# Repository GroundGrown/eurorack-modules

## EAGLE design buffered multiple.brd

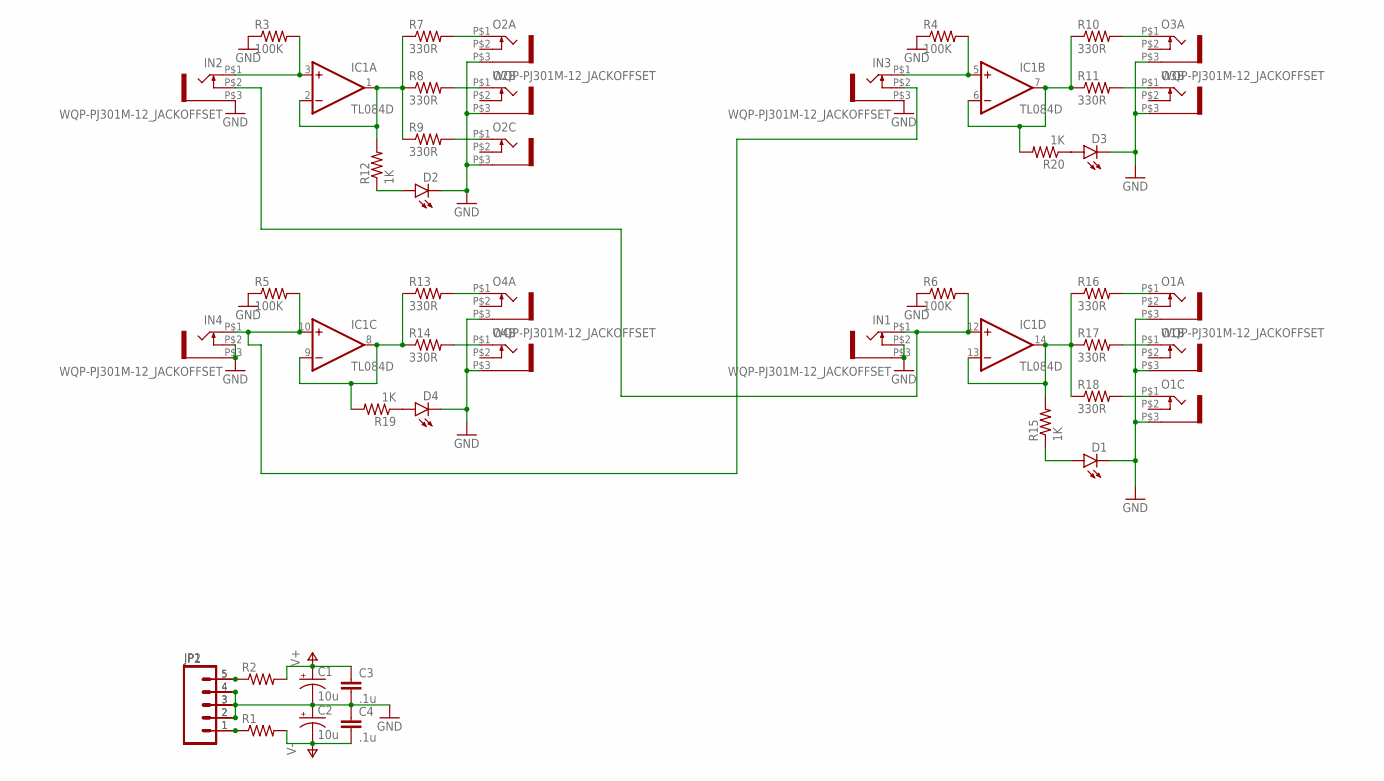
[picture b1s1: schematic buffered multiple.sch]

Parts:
C1, C2: 10u; EIA3216-KIT
C3, C4: .1u; 0805
D1, D2, D3, D4: LED3MM
IC1: TL084D; SO14
IN1, IN2, IN3, IN4: WQP-PJ301M-12_JACKOFFSET
JP1, JP2: M05PTH; 1X05
O1A, O2A, O3A, O4A: WQP-PJ301M-12_JACKOFFSET
O1B, O1C, O2B, O2C, O3B, O4B: WQP-PJ301M-12_JACK
R1, R2: RESISTOR0805-RES; 0805
R3, R4, R5, R6: 100K; 0805
R7, R8, R9, R10, R11, R13, R14, R16, R17, R18: 330R; 0805
R12, R15, R19, R20: 1K; 0805

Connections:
GND: C1.C (-), C2.A (+), C3.2, C4.1, D1.K (C), D2.K (C), D3.K (C), D4.K (C), IN1.P$2 (3), IN1.P$3 (1), IN2.P$3 (1), IN3.P$3 (1), IN4.P$2 (3), IN4.P$3 (1), JP1.2, JP1.3, JP1.4, JP2.2, JP2.3, JP2.4, O1A.P$3 (1), O1B.P$3 (1), O1C.P$3 (1), O2A.P$3 (1), O2B.P$3 (1), O2C.P$3 (1), O3A.P$3 (1), O3B.P$3 (1), O4A.P$3 (1), O4B.P$3 (1), R3.1, R4.1, R5.1, R6.1
unnamed: JP1.1, JP2.1, R1.1
unnamed: JP1.5, JP2.5, R2.1
unnamed: IC1.12 (+IN), IN1.P$1 (2), IN2.P$2 (3), R6.2
unnamed: IC1.10 (+IN), IN3.P$2 (3), IN4.P$1 (2), R5.2
unnamed: IC1.3 (+IN), IN2.P$1 (2), R3.2
unnamed: IC1.5 (+IN), IN3.P$1 (2), R4.2
unnamed: IC1.1 (OUT), IC1.2 (-IN), R7.1, R8.1, R9.1, R12.2
unnamed: O2A.P$1 (2), R7.2
unnamed: O2B.P$1 (2), R8.2
unnamed: O2C.P$1 (2), R9.2
unnamed: IC1.8 (OUT), IC1.9 (-IN), R13.1, R14.1, R19.2
unnamed: O4A.P$1 (2), R13.2
unnamed: O4B.P$1 (2), R14.2
unnamed: IC1.6 (-IN), IC1.7 (OUT), R10.1, R11.1, R20.2
unnamed: O3A.P$1 (2), R10.2
unnamed: O3B.P$1 (2), R11.2
unnamed: D4.A, R19.1
unnamed: IC1.13 (-IN), IC1.14 (OUT), R15.2, R16.1, R17.1, R18.1
unnamed: O1A.P$1 (2), R16.2
unnamed: O1B.P$1 (2), R17.2
unnamed: O1C.P$1 (2), R18.2
unnamed: D3.A, R20.1
unnamed: D1.A, R15.1
unnamed: D2.A, R12.1
V+: C1.A (+), C3.1, IC1.4 (V+), R2.2
V-: C2.C (-), C4.2, IC1.11 (V-), R1.2

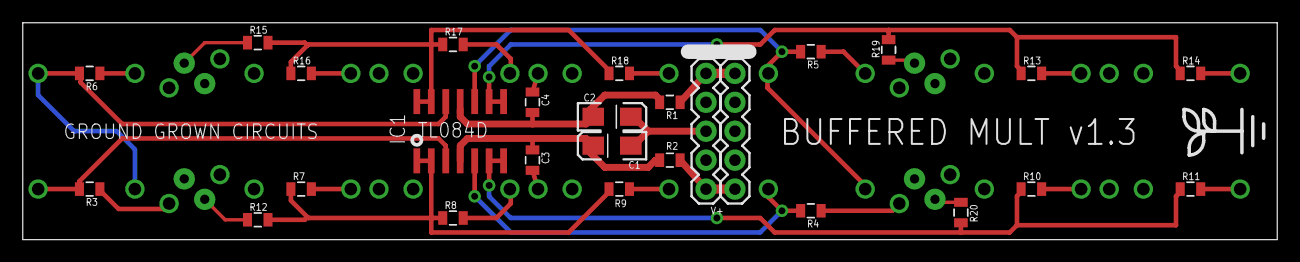
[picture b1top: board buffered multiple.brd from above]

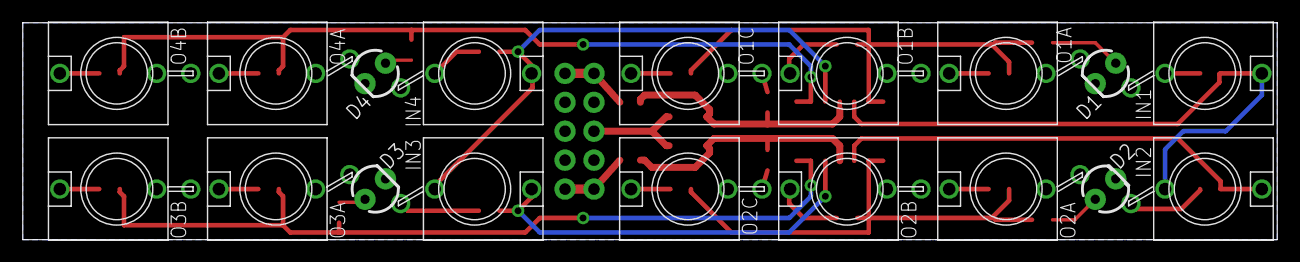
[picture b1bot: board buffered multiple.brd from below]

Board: 2 copper layers, 110.2 x 19.1 mm, 46 parts (18 on the bottom side), 27 nets.

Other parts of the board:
U$1: LOGO_SMALL

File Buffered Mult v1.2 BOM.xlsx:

2 | FERRITE BEAD | R1, R2
10 | 330 ohm | R7, R8, R9, R10, R11, R13, R14, R16, R17, R18
4 | 1K | R12, R15, R19, R20
4 | 100K | R3, R4, R5, R6
2 | .1u | C3, C4
2 | 10u | C1, C2
1 | TL084 | IC1
4 | Bi-color LED | D1, D2, D3, D4
1 | 2x5 pos male .1" Header | JP1
14 | WQP-PJ301M-12_JACK | IN1, IN2, IN3, IN4, O1A, O1B, O1C, O2A, O2B, O2C, O3A, O3B, O4A, O4B

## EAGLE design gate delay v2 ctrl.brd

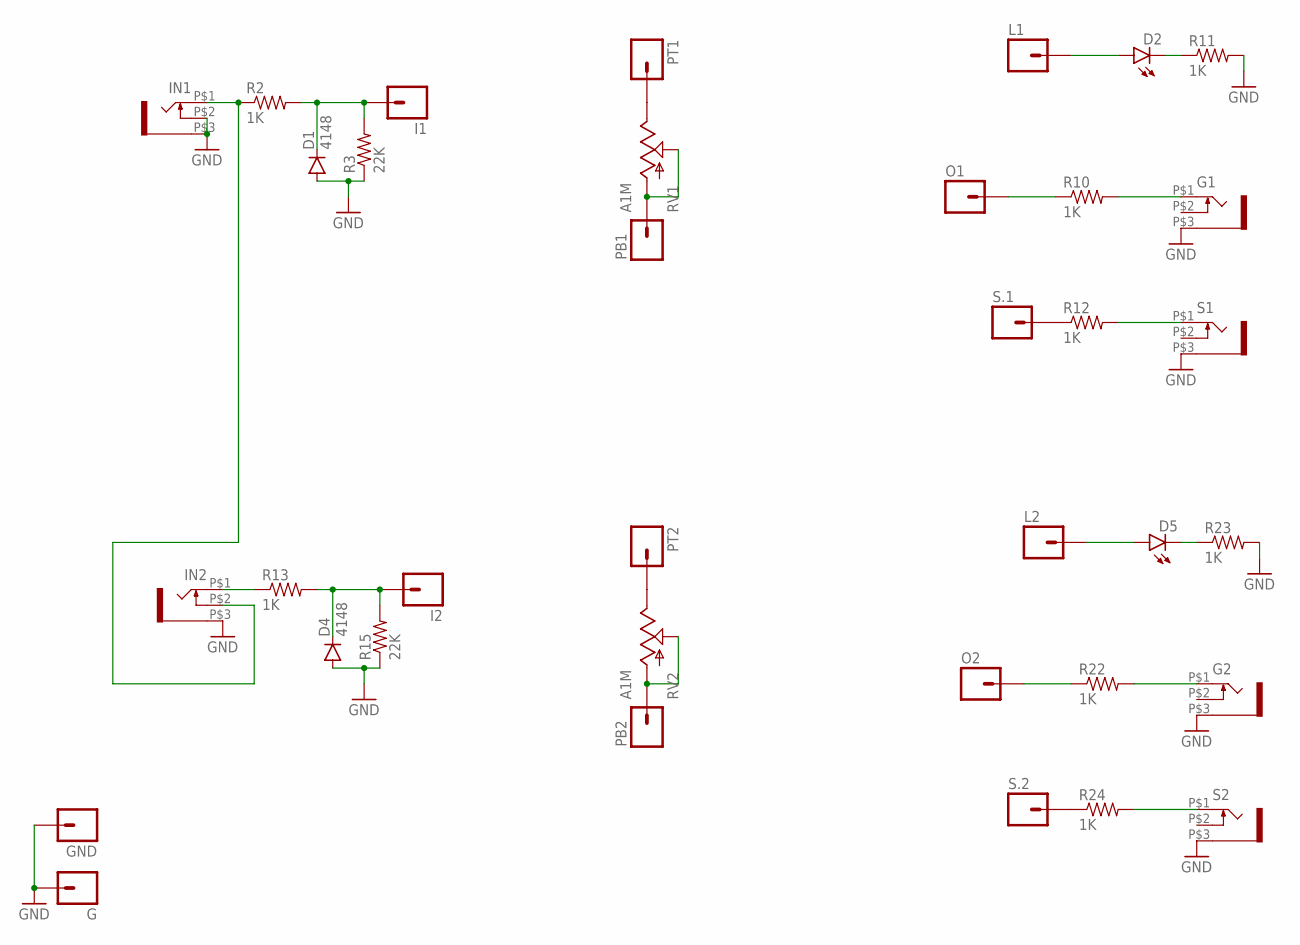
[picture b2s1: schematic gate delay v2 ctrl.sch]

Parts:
D1, D4: 4148; SOD-123
D2, D5: LED3MM
G: M01PTH; 1X01
G1, G2: WQP-PJ301M-12_JACK
GND: M01PTH; 1X01
I1, I2: M01PTH; 1X01
IN1, IN2: WQP-PJ301M-12_JACK
L1, L2: M01PTH; 1X01
O1, O2: M01PTH; 1X01
PB1, PB2: M01PTH; 1X01
PT1, PT2: M01PTH; 1X01
R2, R10, R11, R12, R13, R22, R23, R24: 1K; 0805@1
R3, R15: 22K; 0805@1
RV1, RV2: A1M; ALPS_POT
S1, S2: WQP-PJ301M-12_JACK
S.1, S.2: M01PTH; 1X01

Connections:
GND: D1.A, D4.A, G.1, G1.P$3 (1), G2.P$3 (1), GND.1, IN1.P$2 (3), IN1.P$3 (1), IN2.P$3 (1), R3.1, R11.2, R15.1, R23.2, S1.P$3 (1), S2.P$3 (1)
unnamed: IN1.P$1 (2), IN2.P$2 (3), R2.1
unnamed: D1.C, I1.1, R2.2, R3.2
unnamed: R12.1, S.1.1
unnamed: R24.1, S.2.1
unnamed: IN2.P$1 (2), R13.1
unnamed: PT1.1, RV1.P$1 (E)
unnamed: PB1.1, RV1.P$2 (S), RV1.P$3 (A)
unnamed: O1.1, R10.1
unnamed: PT2.1, RV2.P$1 (E)
unnamed: PB2.1, RV2.P$2 (S), RV2.P$3 (A)
unnamed: D2.A, L1.1
unnamed: D2.K (C), R11.1
unnamed: G1.P$1 (2), R10.2
unnamed: R12.2, S1.P$1 (2)
unnamed: D4.C, I2.1, R13.2, R15.2
unnamed: O2.1, R22.1
unnamed: D5.A, L2.1
unnamed: D5.K (C), R23.1
unnamed: G2.P$1 (2), R22.2
unnamed: R24.2, S2.P$1 (2)

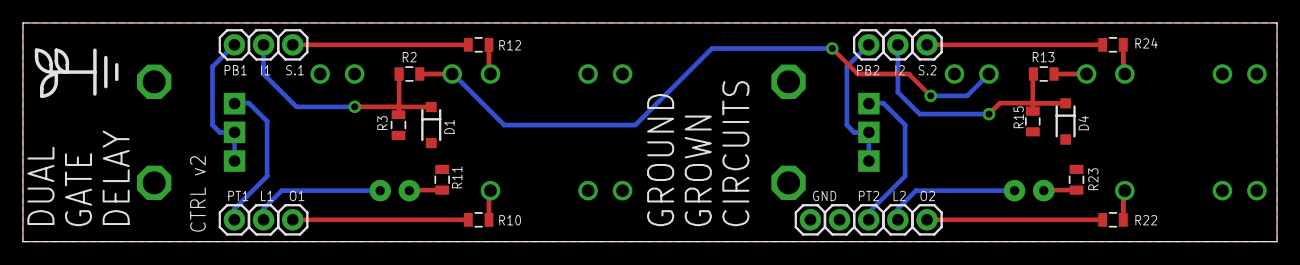
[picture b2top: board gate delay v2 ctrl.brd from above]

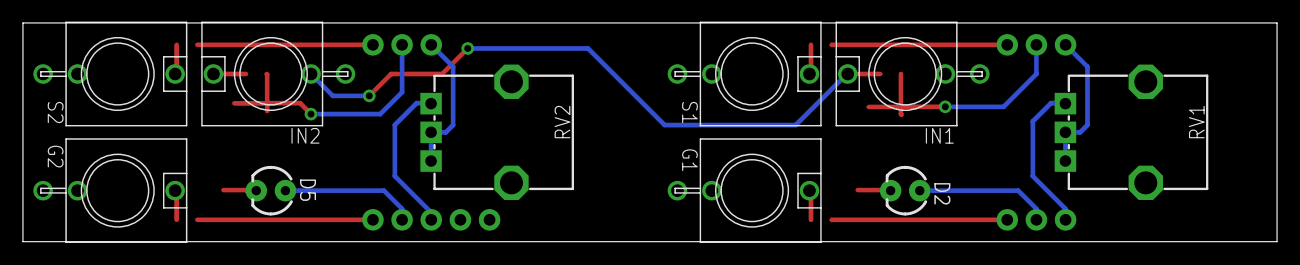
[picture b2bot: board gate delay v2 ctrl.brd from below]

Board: 2 copper layers, 109.2 x 19.1 mm, 37 parts (10 on the bottom side), 21 nets.

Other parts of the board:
U$2: LOGO_SMALL

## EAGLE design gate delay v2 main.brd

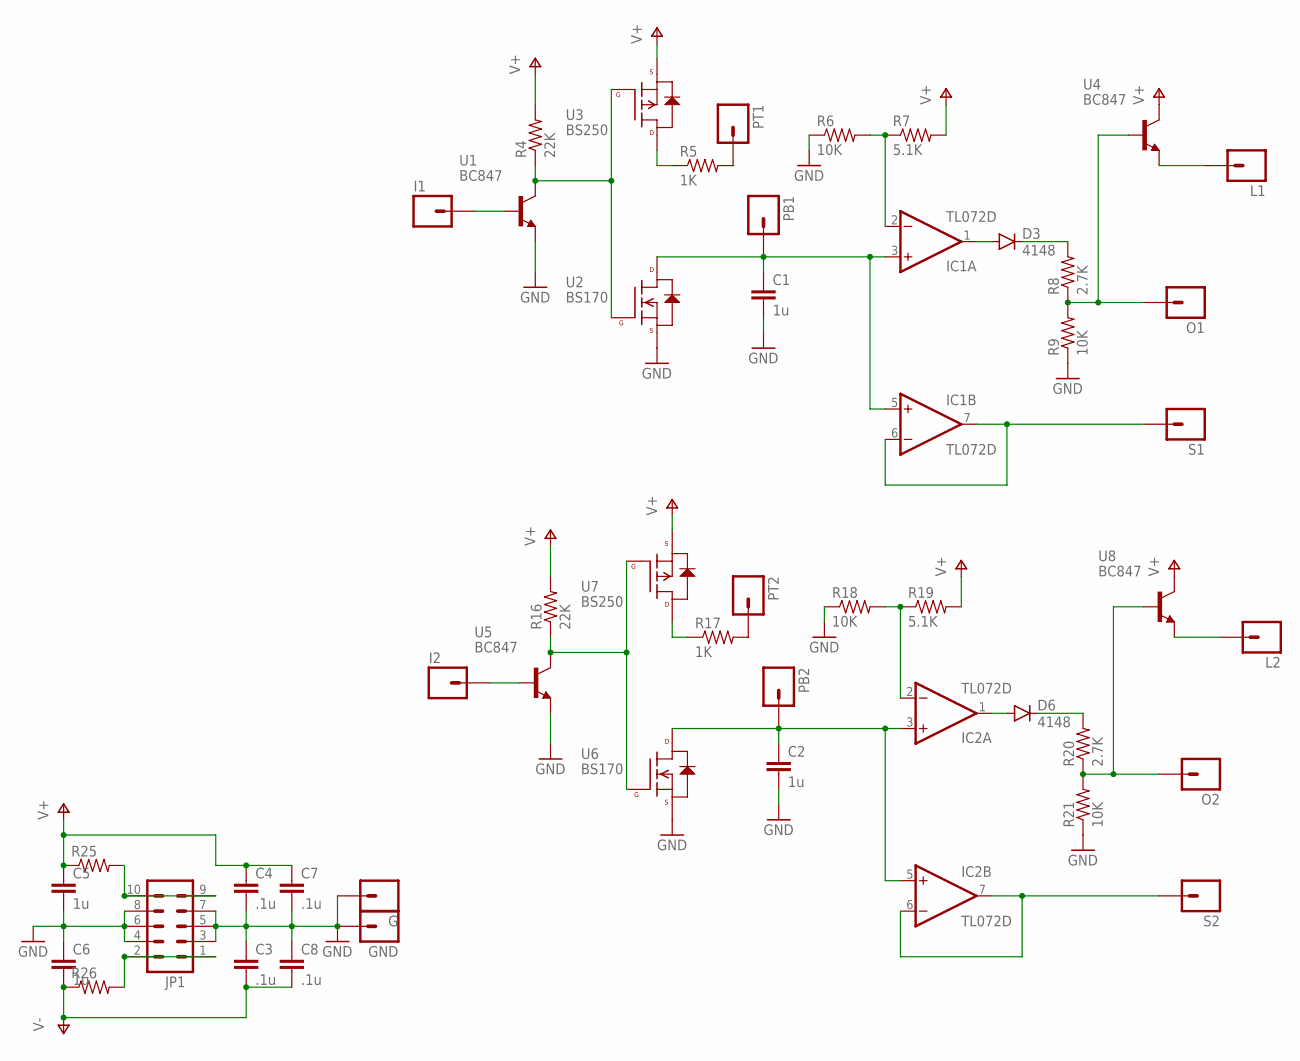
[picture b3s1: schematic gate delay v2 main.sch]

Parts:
C1, C2, C5, C6: 1u; 1206
C3, C4, C7, C8: .1u; 0805
D3, D6: 4148; SOD-123
G: M01PTH; 1X01
GND: M01PTH; 1X01
I1, I2: M01PTH; 1X01
IC1, IC2: TL072D; SO08
JP1: M05X2PTH; AVR_ICSP
L1, L2: M01PTH; 1X01
O1, O2: M01PTH; 1X01
PB1, PB2: M01PTH; 1X01
PT1, PT2: M01PTH; 1X01
R4, R16: 22K; 0805@1
R5, R17: 1K; 0805@1
R6, R9, R18, R21: 10K; 0805@1
R7, R19: 5.1K; 0805@1
R8, R20: 2.7K; 0805@1
R25, R26: RESISTOR0805-RES; 0805@1
S1, S2: M01PTH; 1X01
U1, U4, U5, U8: BC847; SOT23
U2, U6: BS170; SOT23-3
U3, U7: BS250; SOT23-3

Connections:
GND: C1.2, C2.2, C3.1, C4.2, C5.2, C6.1, C7.2, C8.1, G.1, GND.1, JP1.3, JP1.4, JP1.5, JP1.6, JP1.7, JP1.8, R6.1, R9.1, R18.1, R21.1, U1.2 (E), U2.2 (S), U5.2 (E), U6.2 (S)
unnamed: PT1.1, R5.2
unnamed: I1.1, U1.1 (B)
unnamed: R4.1, U1.3 (C), U2.1 (G), U3.1 (G)
unnamed: R5.1, U3.3 (D)
unnamed: PT2.1, R17.2
unnamed: C1.1, IC1.3 (+IN), IC1.5 (+IN), PB1.1, U2.3 (D)
unnamed: O1.1, R8.1, R9.2, U4.1 (B)
unnamed: D3.A, IC1.1 (OUT)
unnamed: IC1.2 (-IN), R6.2, R7.1
unnamed: D3.C, R8.2
unnamed: L1.1, U4.2 (E)
unnamed: IC1.6 (-IN), IC1.7 (OUT), S1.1
unnamed: I2.1, U5.1 (B)
unnamed: R16.1, U5.3 (C), U6.1 (G), U7.1 (G)
unnamed: R17.1, U7.3 (D)
unnamed: C2.1, IC2.3 (+IN), IC2.5 (+IN), PB2.1, U6.3 (D)
unnamed: IC2.2 (-IN), R18.2, R19.1
unnamed: O2.1, R20.1, R21.2, U8.1 (B)
unnamed: D6.A, IC2.1 (OUT)
unnamed: D6.C, R20.2
unnamed: L2.1, U8.2 (E)
unnamed: IC2.6 (-IN), IC2.7 (OUT), S2.1
unnamed: JP1.1, JP1.2, R26.2
unnamed: JP1.9, JP1.10, R25.2
V+: C4.1, C5.1, C7.1, IC1.8 (V+), IC2.8 (V+), R4.2, R7.2, R16.2, R19.2, R25.1, U3.2 (S), U4.3 (C), U7.2 (S), U8.3 (C)
V-: C3.2, C6.2, C8.2, IC1.4 (V-), IC2.4 (V-), R26.1

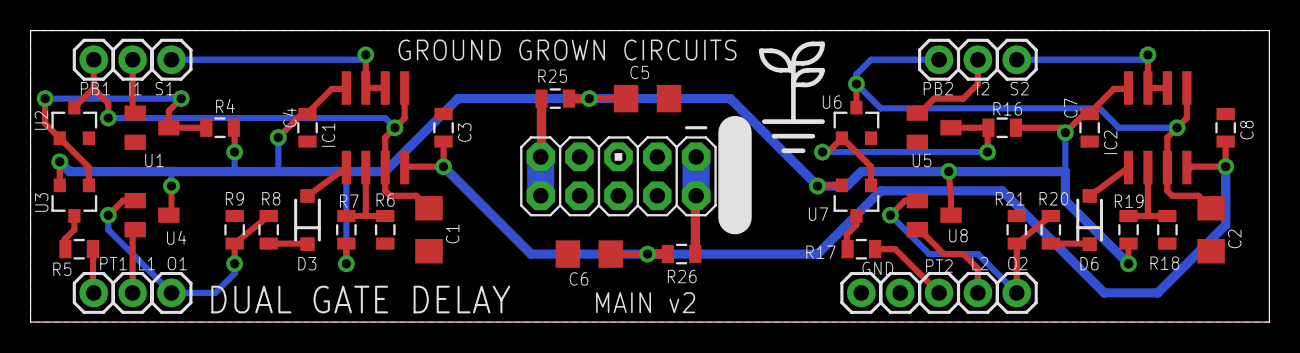
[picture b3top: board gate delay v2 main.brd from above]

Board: 2 copper layers, 81.0 x 19.1 mm, 50 parts (0 on the bottom side), 27 nets.

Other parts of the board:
U$2: LOGO_SMALL

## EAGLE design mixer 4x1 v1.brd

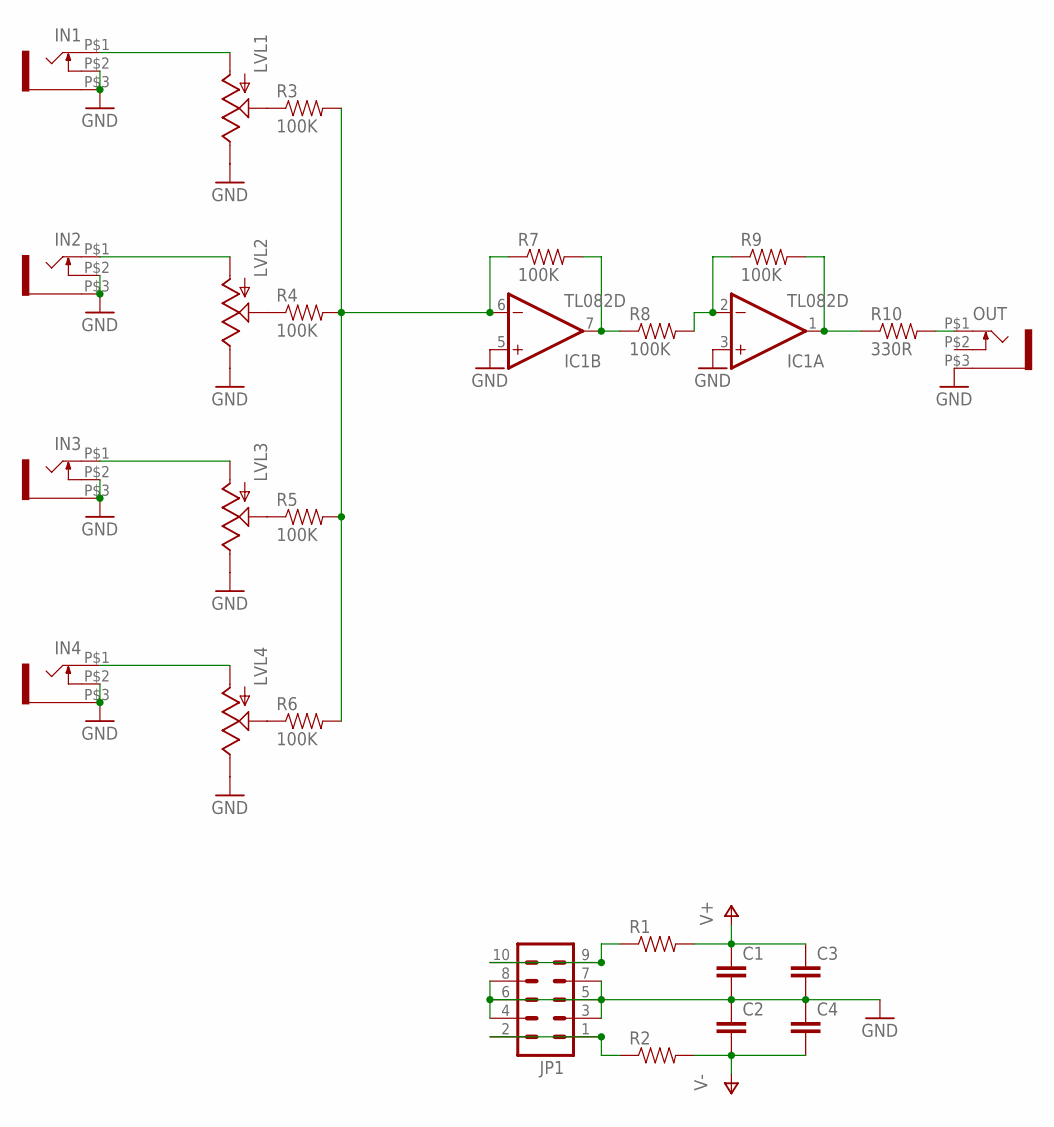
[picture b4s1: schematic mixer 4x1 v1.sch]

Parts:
C1, C2: CAP1206; 1206
C3, C4: CAP0805; 0805
IC1: TL082D; SO08
IN1, IN2, IN3, IN4: WQP-PJ301M-12_JACK
JP1: M05X2PTH; AVR_ICSP
LVL1, LVL2, LVL3, LVL4: POT; ALPS_POT
OUT: WQP-PJ301M-12_JACK
R1, R2: RESISTOR0805-RES; 0805
R3, R4, R5, R6, R7, R8, R9: 100K; 0805
R10: 330R; 0805

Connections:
GND: C1.2, C2.1, C3.2, C4.1, IC1.3 (+IN), IC1.5 (+IN), IN1.P$2 (3), IN1.P$3 (1), IN2.P$2 (3), IN2.P$3 (1), IN3.P$2 (3), IN3.P$3 (1), IN4.P$2 (3), IN4.P$3 (1), JP1.3, JP1.4, JP1.5, JP1.6, JP1.7, JP1.8, LVL1.P$1 (E), LVL2.P$1 (E), LVL3.P$1 (E), LVL4.P$1 (E), OUT.P$3 (1)
unnamed: LVL1.P$2 (S), R3.1
unnamed: IN2.P$1 (2), LVL2.P$3 (A)
unnamed: JP1.9, JP1.10, R1.1
unnamed: LVL2.P$2 (S), R4.1
unnamed: JP1.1, JP1.2, R2.1
unnamed: IN3.P$1 (2), LVL3.P$3 (A)
unnamed: IN1.P$1 (2), LVL1.P$3 (A)
unnamed: LVL3.P$2 (S), R5.1
unnamed: IN4.P$1 (2), LVL4.P$3 (A)
unnamed: LVL4.P$2 (S), R6.1
unnamed: IC1.6 (-IN), R3.2, R4.2, R5.2, R6.2, R7.1
unnamed: IC1.7 (OUT), R7.2, R8.1
unnamed: IC1.2 (-IN), R8.2, R9.1
unnamed: IC1.1 (OUT), R9.2, R10.1
unnamed: OUT.P$1 (2), R10.2
V+: C1.1, C3.1, IC1.8 (V+), R1.2
V-: C2.2, C4.2, IC1.4 (V-), R2.2

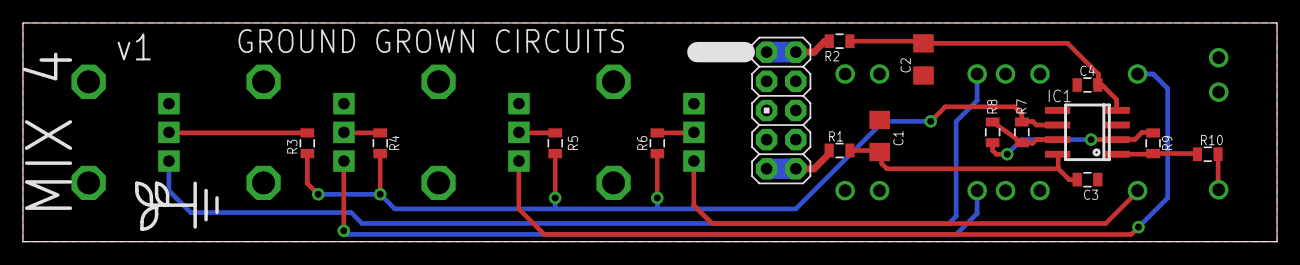
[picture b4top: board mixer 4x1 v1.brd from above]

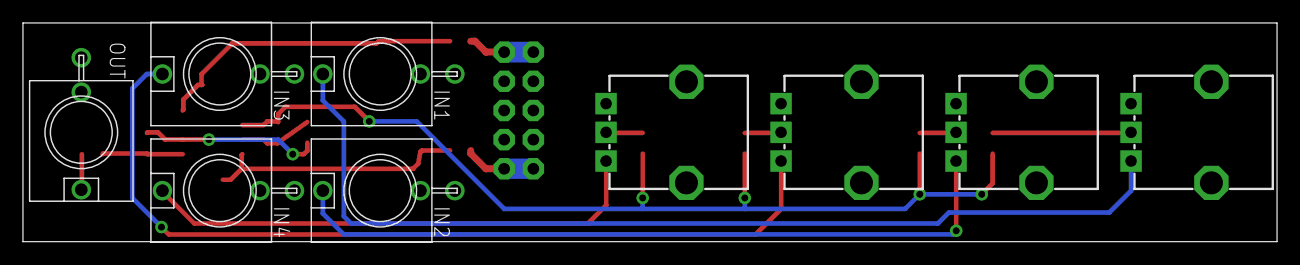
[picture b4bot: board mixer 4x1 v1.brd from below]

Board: 2 copper layers, 109.2 x 19.1 mm, 26 parts (9 on the bottom side), 18 nets.

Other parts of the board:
U$1: LOGO_SMALL

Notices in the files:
parts and their libraries:
SparkFun-Passives: Licensing: Creative Commons ShareAlike 4.0 International - https://creativecommons.org/licenses/by-sa/4.0
